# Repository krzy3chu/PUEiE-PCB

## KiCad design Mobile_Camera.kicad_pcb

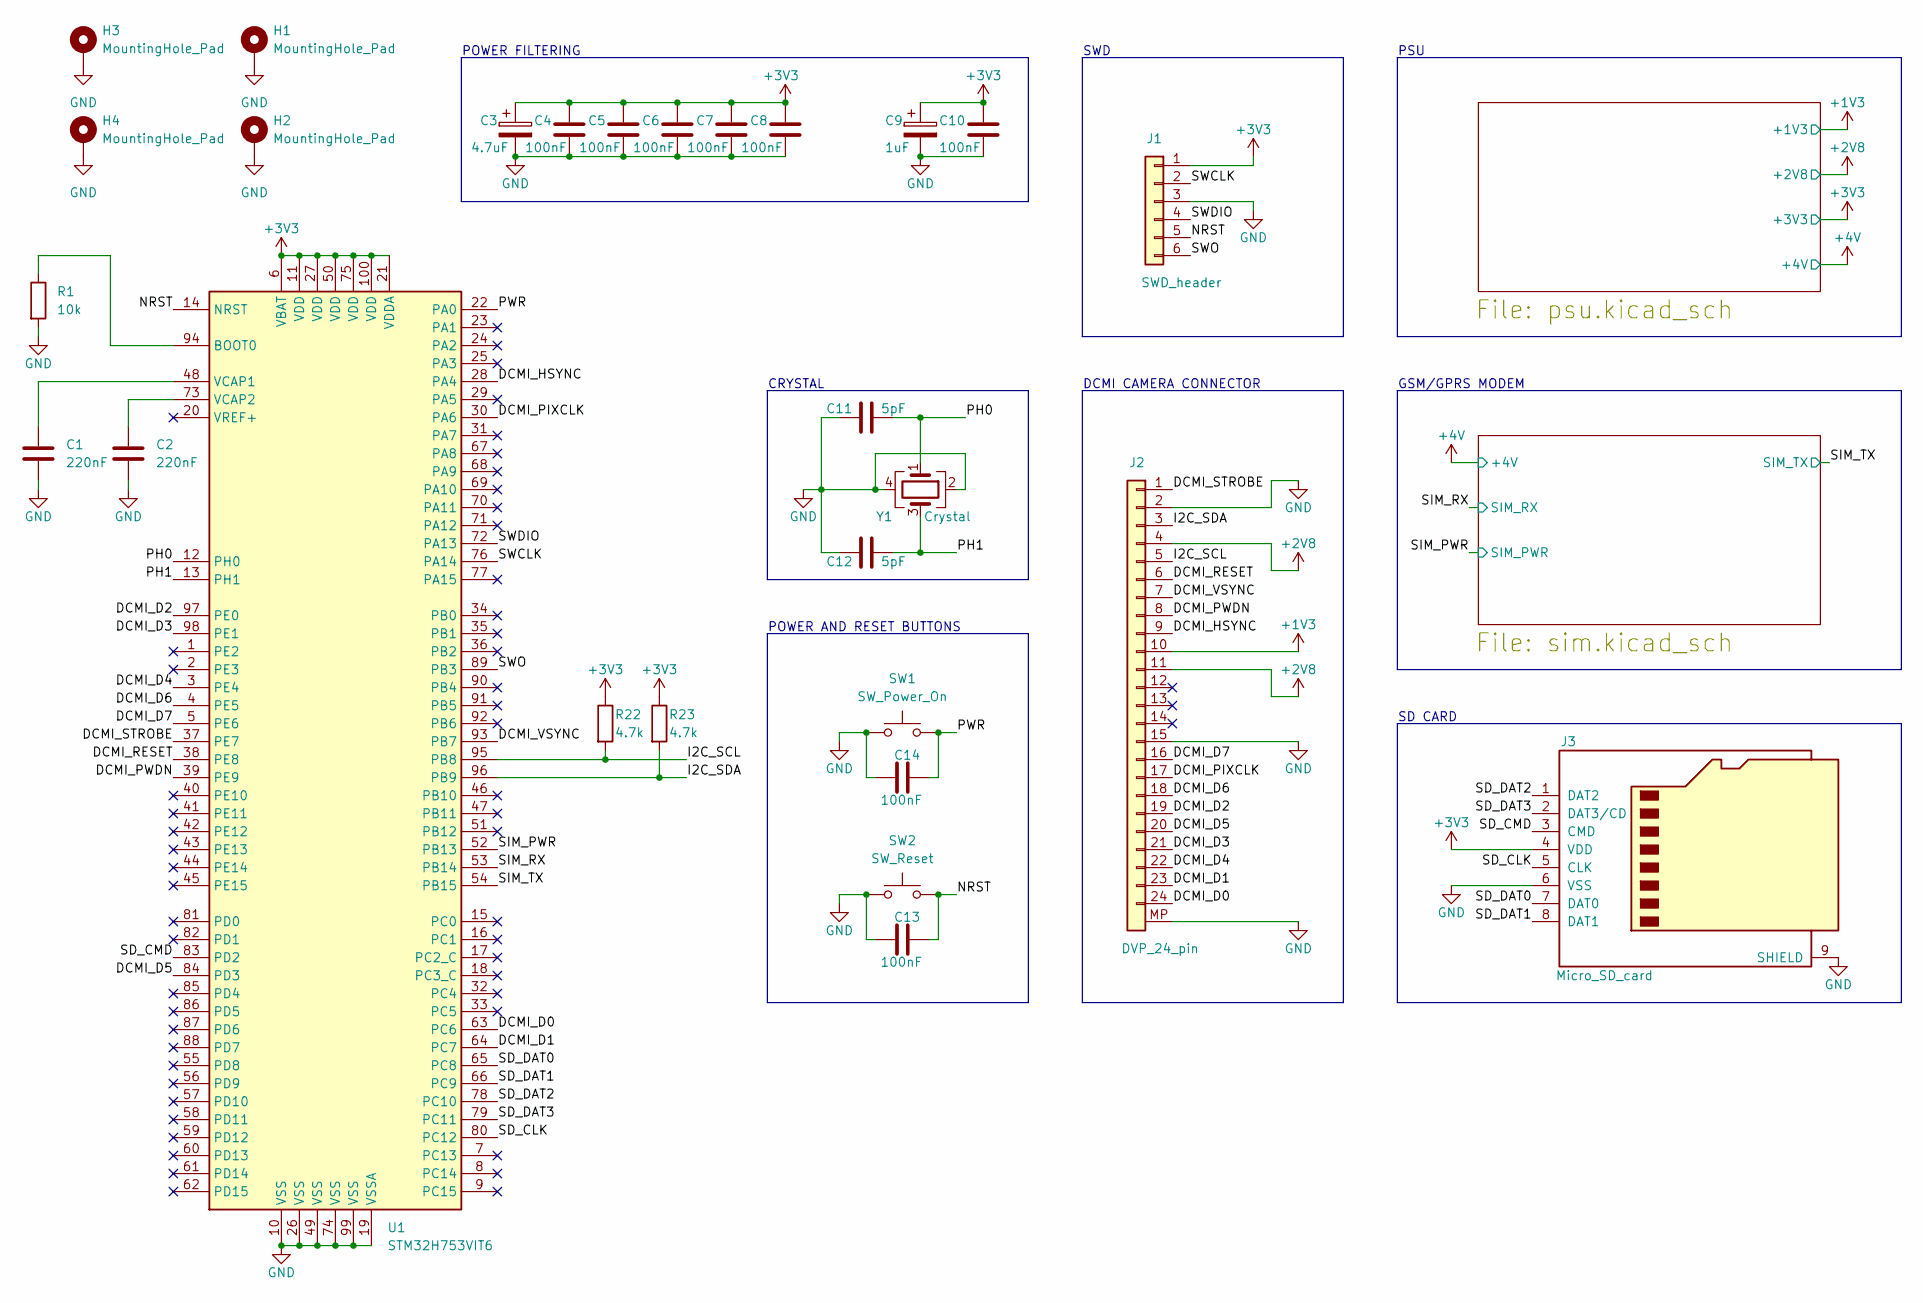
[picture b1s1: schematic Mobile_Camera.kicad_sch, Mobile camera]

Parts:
C1, C2: 220nF; C_0603_1608Metric_Pad1.08x0.95mm_HandSolder
C3: 4.7uF; CP_Elec_4x5.4
C4, C5, C6, C7, C8, C10, C13, C14: 100nF; C_0603_1608Metric_Pad1.08x0.95mm_HandSolder
C9: 1uF; CP_Elec_4x5.4
C11, C12: 5pF; C_0603_1608Metric_Pad1.08x0.95mm_HandSolder
H1, H2, H3, H4: MountingHole_Pad; MountingHole_3.2mm_M3_DIN965_Pad
J1: SWD_header; PinHeader_1x06_P2.54mm_Vertical
J2: DVP_24_pin; TE_2-1734839-4_1x24-1MP_P0.5mm_Horizontal
J3: Micro_SD_card; microSD_HC_Wuerth_693072010801
R1: 10k; R_0603_1608Metric_Pad0.98x0.95mm_HandSolder
R22, R23: 4.7k; R_0603_1608Metric_Pad0.98x0.95mm_HandSolder
SW1: SW_Power_On; SW_SPST_Omron_B3FS-101xP
SW2: SW_Reset; SW_SPST_Omron_B3FS-101xP
U1: STM32H753VIT6; LQFP-100_14x14mm_P0.5mm
Y1: Crystal; Crystal_SMD_SeikoEpson_TSX3225-4Pin_3.2x2.5mm_HandSoldering

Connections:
+1V35: J2.10; also elsewhere on the board
+2V8: J2.4, J2.11; also elsewhere on the board
+3V3: C3.1, C4.1, C5.1, C6.1, C7.1, C8.1, C9.1, C10.1, J1.1, J3.4 (VDD), R22.1, R23.1, U1.6 (VBAT), U1.11 (VDD), U1.21 (VDDA), U1.27 (VDD), U1.50 (VDD), U1.75 (VDD), U1.100 (VDD); also elsewhere on the board
/DCMI_D0: J2.24, U1.63 (PC6)
/DCMI_D1: J2.23, U1.64 (PC7)
/DCMI_D2: J2.19, U1.97 (PE0)
/DCMI_D3: J2.21, U1.98 (PE1)
/DCMI_D4: J2.22, U1.3 (PE4)
/DCMI_D5: J2.20, U1.84 (PD3)
/DCMI_D6: J2.18, U1.4 (PE5)
/DCMI_D7: J2.16, U1.5 (PE6)
/DCMI_HSYNC: J2.9, U1.28 (PA4)
/DCMI_PIXCLK: J2.17, U1.30 (PA6)
/DCMI_PWDN: J2.8, U1.39 (PE9)
/DCMI_RESET: J2.6, U1.38 (PE8)
/DCMI_STROBE: J2.1, U1.37 (PE7)
/DCMI_VSYNC: J2.7, U1.93 (PB7)
/I2C_SCL: J2.5, R22.2, U1.95 (PB8)
/I2C_SDA: J2.3, R23.2, U1.96 (PB9)
/NRST: C13.1, J1.5, SW2.2, U1.14 (NRST)
/PH0: C11.2, U1.12 (PH0), Y1.1
/PH1: C12.2, U1.13 (PH1), Y1.3
/PWR: C14.1, SW1.2, U1.22 (PA0)
/SD_CLK: J3.5 (CLK), U1.80 (PC12)
/SD_CMD: J3.3 (CMD), U1.83 (PD2)
/SD_DAT0: J3.7 (DAT0), U1.65 (PC8)
/SD_DAT1: J3.8 (DAT1), U1.66 (PC9)
/SD_DAT2: J3.1 (DAT2), U1.78 (PC10)
/SD_DAT3: J3.2 (DAT3/CD), U1.79 (PC11)
/SIM_PWR: U1.52 (PB13); also elsewhere on the board
/SIM_RX: U1.53 (PB14); also elsewhere on the board
/SIM_TX: U1.54 (PB15); also elsewhere on the board
/SWCLK: J1.2, U1.76 (PA14)
/SWDIO: J1.4, U1.72 (PA13)
/SWO: J1.6, U1.89 (PB3)
GND: C1.2, C2.2, C3.2, C4.2, C5.2, C6.2, C7.2, C8.2, C9.2, C10.2, C11.1, C12.1, C13.2, C14.2, H1.1, H2.1, H3.1, H4.1, J1.3, J2.2, J2.15, J2.MP, J3.6 (VSS), J3.9 (SHIELD), R1.2, SW1.1, SW2.1, U1.10 (VSS), U1.19 (VSSA), U1.26 (VSS), U1.49 (VSS), U1.74 (VSS), U1.99 (VSS), Y1.2, Y1.4; also elsewhere on the board
unnamed: R1.1, U1.94 (BOOT0)
unnamed: C1.1, U1.48 (VCAP1)
unnamed: C2.1, U1.73 (VCAP2)

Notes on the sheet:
SD CARD
DCMI CAMERA CONNECTOR
PSU
GSM/GPRS MODEM
SWD
POWER FILTERING
POWER AND RESET BUTTONS
CRYSTAL

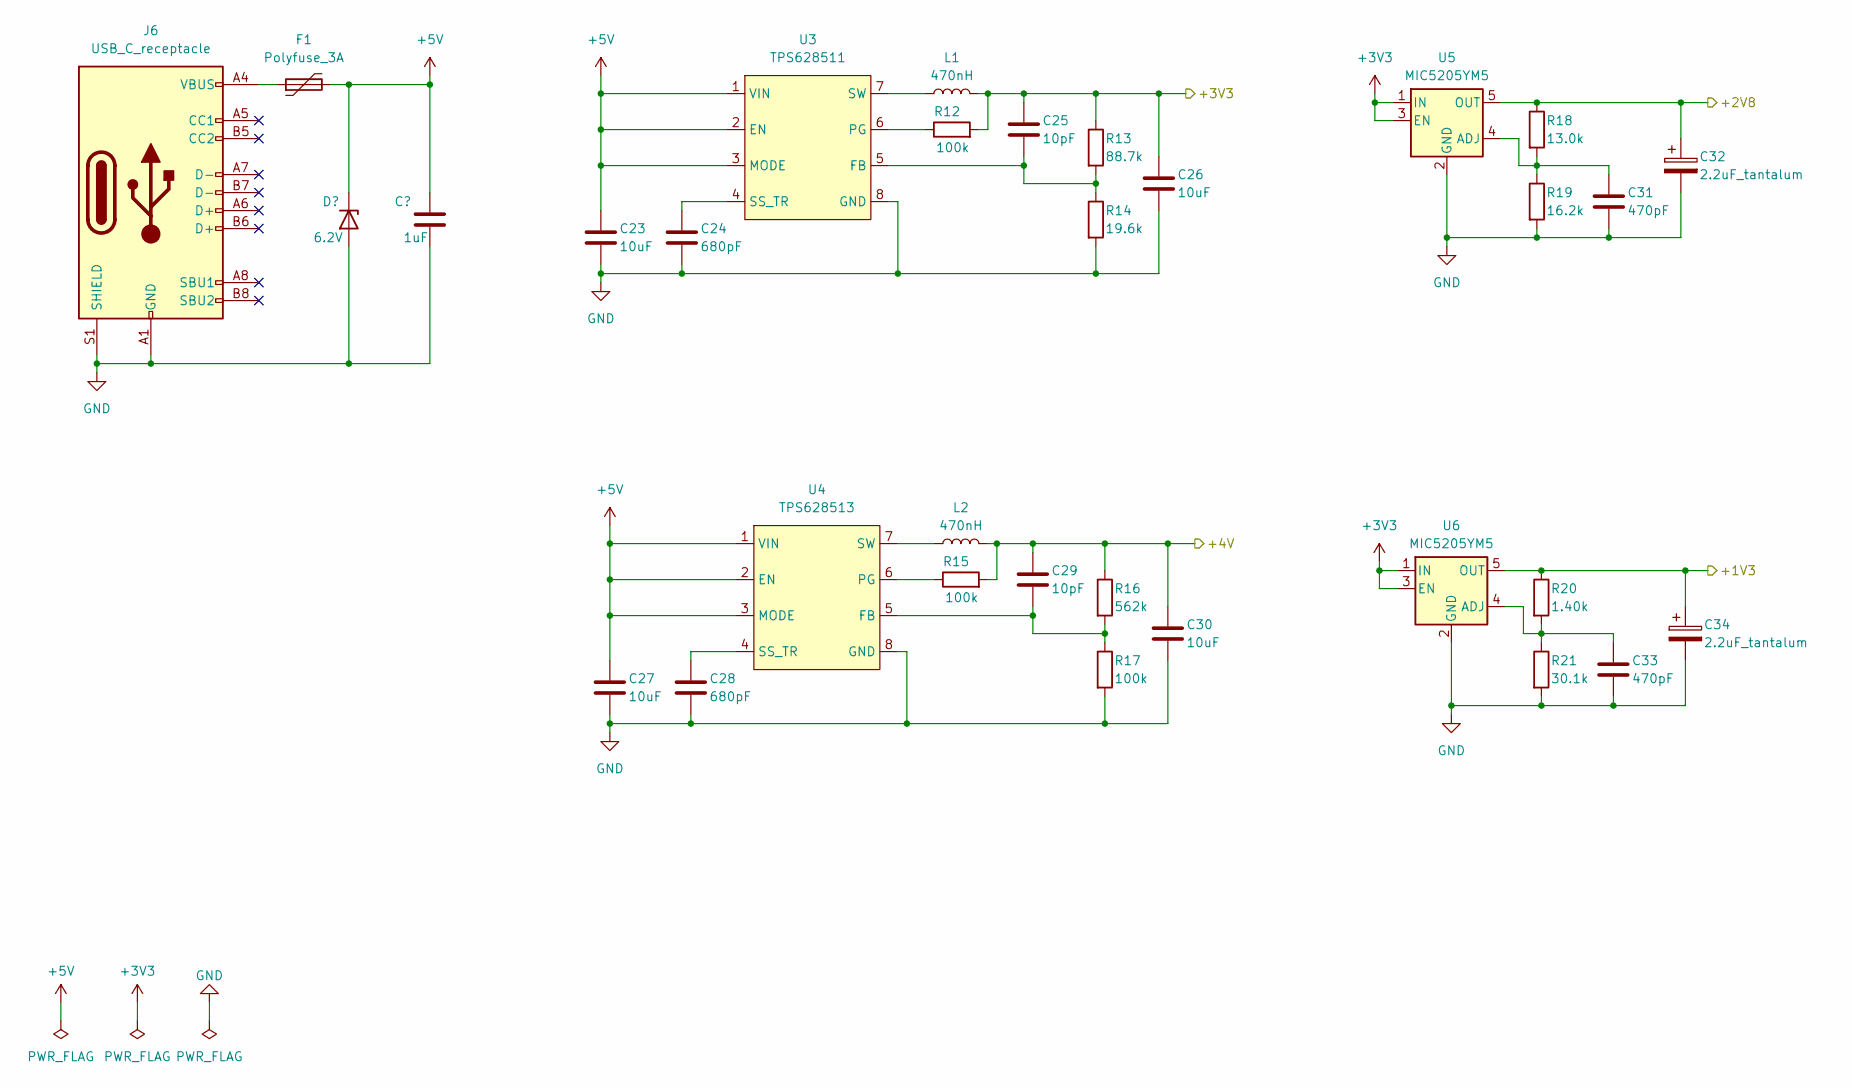
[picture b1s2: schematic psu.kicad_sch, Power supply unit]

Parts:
C22: 1uF; C_0603_1608Metric_Pad1.08x0.95mm_HandSolder
C23, C26, C27, C30: 10uF; C_0603_1608Metric_Pad1.08x0.95mm_HandSolder
C24, C28: 680pF; C_0603_1608Metric_Pad1.08x0.95mm_HandSolder
C25, C29: 10pF; C_0603_1608Metric_Pad1.08x0.95mm_HandSolder
C31, C33: 470pF; C_0603_1608Metric_Pad1.08x0.95mm_HandSolder
C32, C34: 2.2uF_tantalum; C_0603_1608Metric_Pad1.08x0.95mm_HandSolder
D5: 6.2V; D_SOD-323_HandSoldering
F1: Polyfuse_3A; Fuse_1812_4532Metric_Pad1.30x3.40mm_HandSolder
J6: USB_C_receptacle; USB_C_Receptacle_JAE_DX07S016JA1R1500
L1, L2: 470nH; L_Vishay_IHLP-1616
R12, R15, R17: 100k; R_0603_1608Metric_Pad0.98x0.95mm_HandSolder
R13: 88.7k; R_0603_1608Metric_Pad0.98x0.95mm_HandSolder
R14: 19.6k; R_0603_1608Metric_Pad0.98x0.95mm_HandSolder
R16: 562k; R_0603_1608Metric_Pad0.98x0.95mm_HandSolder
R18: 13.0k; R_0603_1608Metric_Pad0.98x0.95mm_HandSolder
R19: 16.2k; R_0603_1608Metric_Pad0.98x0.95mm_HandSolder
R20: 1.40k; R_0603_1608Metric_Pad0.98x0.95mm_HandSolder
R21: 30.1k; R_0603_1608Metric_Pad0.98x0.95mm_HandSolder
U3: TPS628511; SOT-583
U4: TPS628513; SOT-583
U5, U6: MIC5205YM5; SOT-23-5

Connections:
+1V35: C34.1, R20.1, U6.5 (OUT); also elsewhere on the board
+2V8: C32.1, R18.1, U5.5 (OUT); also elsewhere on the board
+3V3: C25.1, C26.1, L1.2, R12.2, R13.1, U5.1 (IN), U5.3 (EN), U6.1 (IN), U6.3 (EN); also elsewhere on the board
+4V: C29.1, C30.1, L2.2, R15.2, R16.1; also elsewhere on the board
+5V: C22.1, C23.1, C27.1, D5.1 (K), F1.2, U3.1 (VIN), U3.2 (EN), U3.3 (MODE), U4.1 (VIN), U4.2 (EN), U4.3 (MODE)
GND: C22.2, C23.2, C24.2, C26.2, C27.2, C28.2, C30.2, C31.2, C32.2, C33.2, C34.2, D5.2 (A), J6.A1 (GND), J6.A12 (GND), J6.B1 (GND), J6.B12 (GND), J6.S1 (SHIELD), R14.2, R17.2, R19.2, R21.2, U3.8 (GND), U4.8 (GND), U5.2 (GND), U6.2 (GND); also elsewhere on the board
unnamed: F1.1, J6.A4 (VBUS), J6.A9 (VBUS), J6.B4 (VBUS), J6.B9 (VBUS)
unnamed: C25.2, R13.2, R14.1, U3.5 (FB)
unnamed: R12.1, U3.6 (PG)
unnamed: C24.1, U3.4 (SS_TR)
unnamed: L1.1, U3.7 (SW)
unnamed: C29.2, R16.2, R17.1, U4.5 (FB)
unnamed: R15.1, U4.6 (PG)
unnamed: C28.1, U4.4 (SS_TR)
unnamed: L2.1, U4.7 (SW)
unnamed: C31.1, R18.2, R19.1, U5.4 (ADJ)
unnamed: C33.1, R20.2, R21.1, U6.4 (ADJ)

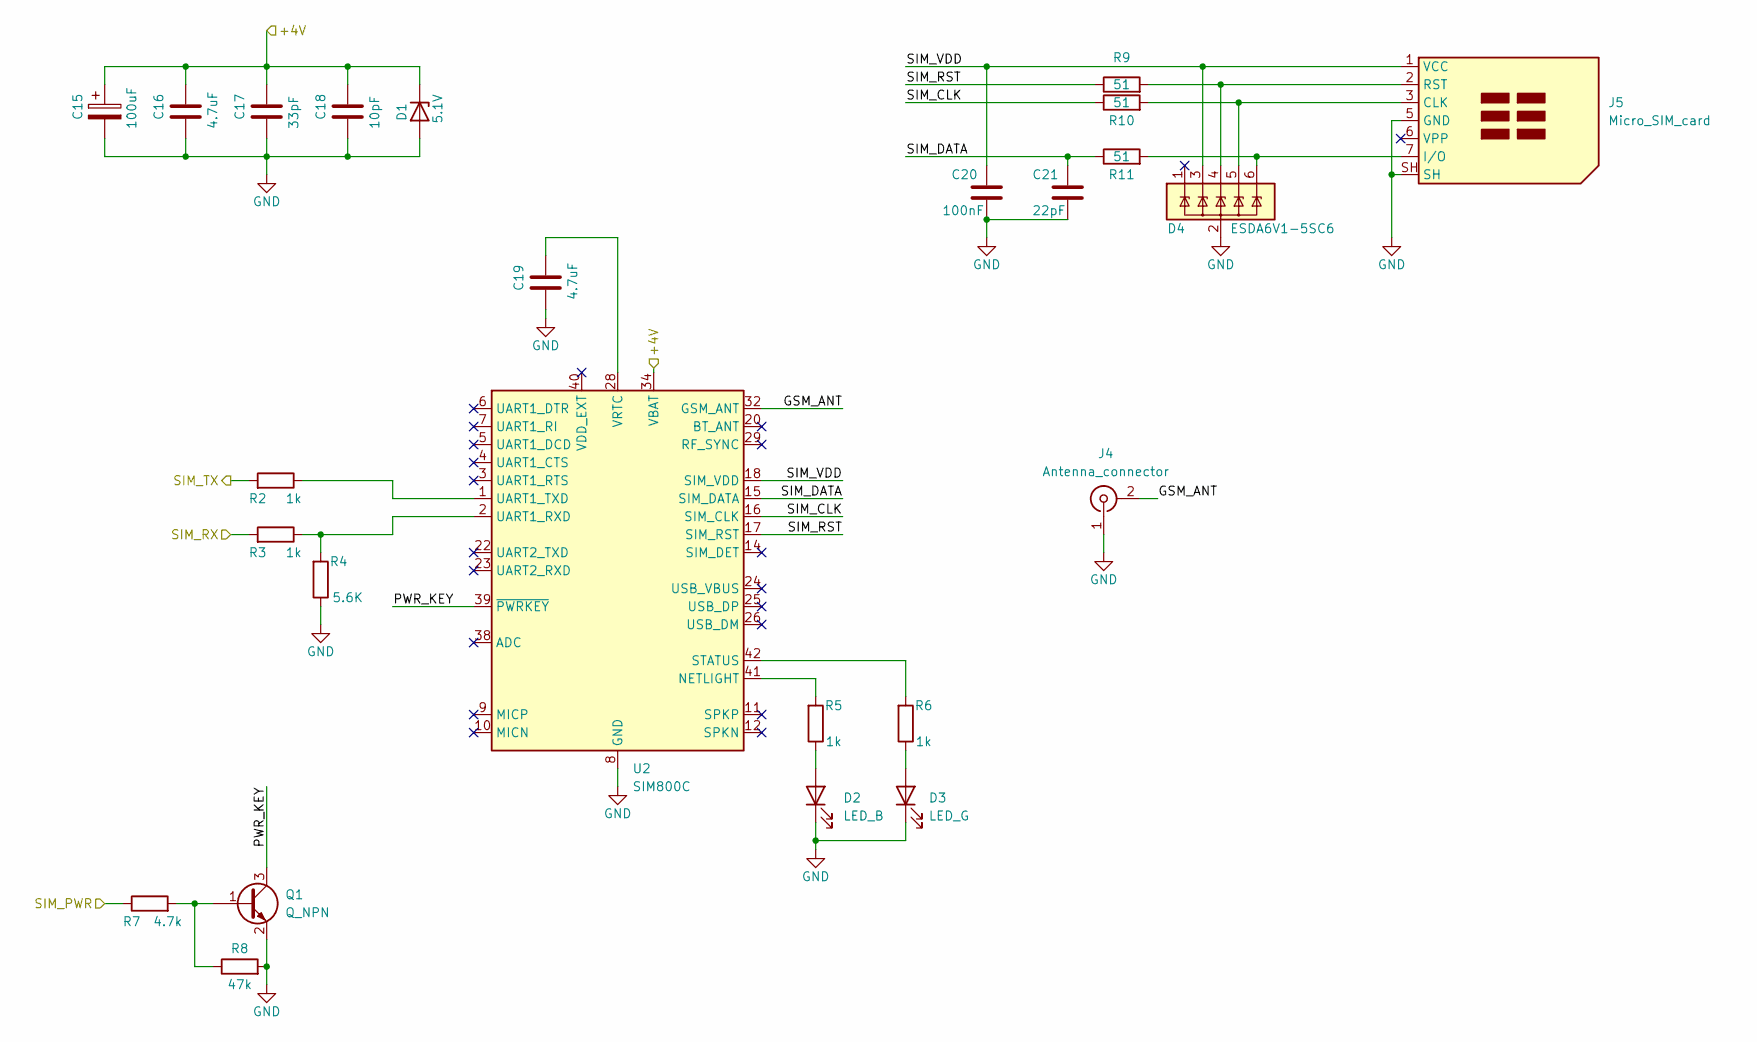
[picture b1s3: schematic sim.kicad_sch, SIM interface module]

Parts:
C15: 100uF; CP_Elec_5x5.4
C16, C19: 4.7uF; C_0603_1608Metric_Pad1.08x0.95mm_HandSolder
C17: 33pF; C_0603_1608Metric_Pad1.08x0.95mm_HandSolder
C18: 10pF; C_0603_1608Metric_Pad1.08x0.95mm_HandSolder
C20: 100nF; C_0603_1608Metric_Pad1.08x0.95mm_HandSolder
C21: 22pF; C_0603_1608Metric_Pad1.08x0.95mm_HandSolder
D1: 5.1V; D_SOD-323_HandSoldering
D2: LED_B; LED_0603_1608Metric
D3: LED_G; LED_0603_1608Metric
D4: ESDA6V1-5SC6; SOT-23-6
J4: Antenna_connector; U.FL_Hirose_U.FL-R-SMT-1_Vertical
J5: Micro_SIM_card; microSIM_JAE_SF53S006VCBR2000
Q1: Q_NPN; SOT-23_Handsoldering
R2, R3, R5, R6: 1k; R_0603_1608Metric_Pad0.98x0.95mm_HandSolder
R4: 5.6K; R_0603_1608Metric_Pad0.98x0.95mm_HandSolder
R7: 4.7k; R_0603_1608Metric_Pad0.98x0.95mm_HandSolder
R8: 47k; R_0603_1608Metric_Pad0.98x0.95mm_HandSolder
R9, R10, R11: 51; R_0603_1608Metric_Pad0.98x0.95mm_HandSolder
U2: SIM800C; SIMCom_SIM800C

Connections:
+4V: C15.1, C16.1, C17.1, C18.1, D1.1 (K), U2.34 (VBAT), U2.35 (VBAT); also elsewhere on the board
/SIM/GSM_ANT: J4.2 (Ext), U2.32 (GSM_ANT)
/SIM/PWR_KEY: Q1.3 (C), U2.39 (~PWRKEY)
/SIM/SIM_CLK: R10.1, U2.16 (SIM_CLK)
/SIM/SIM_DATA: C21.1, R11.1, U2.15 (SIM_DATA)
/SIM/SIM_RST: R9.1, U2.17 (SIM_RST)
/SIM/SIM_VDD: C20.1, D4.3 (IO2), J5.1 (VCC), U2.18 (SIM_VDD)
/SIM_PWR: R7.1; also elsewhere on the board
/SIM_RX: R3.2; also elsewhere on the board
/SIM_TX: R2.2; also elsewhere on the board
GND: C15.2, C16.2, C17.2, C18.2, C19.2, C20.2, C21.2, D1.2 (A), D2.1 (K), D3.1 (K), D4.2 (GND), J4.1 (In), J5.5 (GND), J5.SH, Q1.2 (E), R4.1, R8.2, U2.8 (GND), U2.13 (GND), U2.19 (GND), U2.21 (GND), U2.27 (GND), U2.30 (GND), U2.31 (GND), U2.33 (GND), U2.36 (GND), U2.37 (GND); also elsewhere on the board
unnamed: D2.2 (A), R5.1
unnamed: D3.2 (A), R6.1
unnamed: D4.4 (IO3), J5.2 (RST), R9.2
unnamed: D4.5 (IO4), J5.3 (CLK), R10.2
unnamed: D4.6 (IO5), J5.7 (I/O), R11.2
unnamed: Q1.1 (B), R7.2, R8.1
unnamed: R5.2, U2.41 (NETLIGHT)
unnamed: R6.2, U2.42 (STATUS)
unnamed: R3.1, R4.2, U2.2 (UART1_RXD)
unnamed: R2.1, U2.1 (UART1_TXD)
unnamed: C19.1, U2.28 (VRTC)

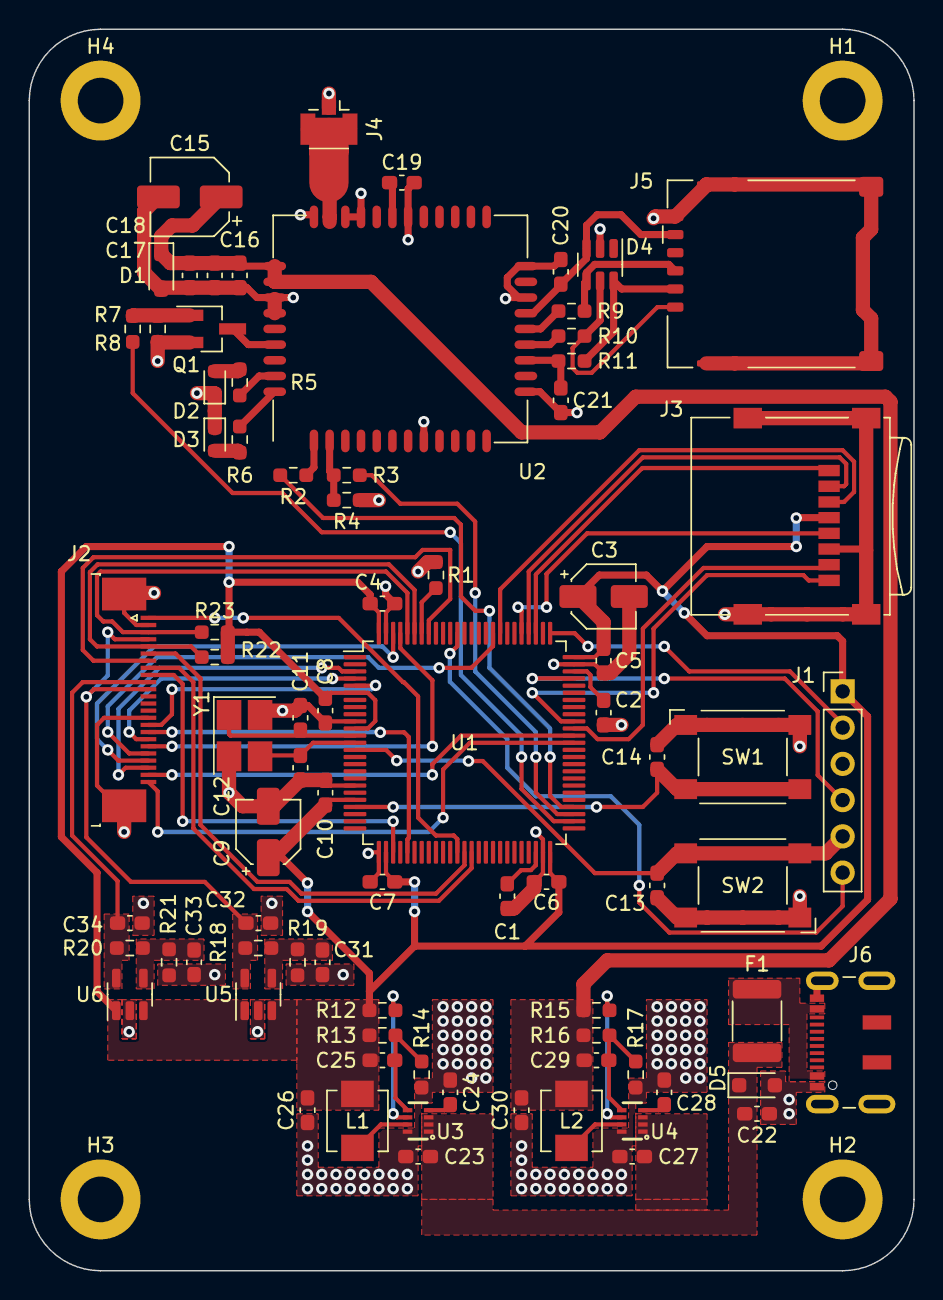
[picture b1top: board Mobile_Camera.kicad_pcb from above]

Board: 2 copper layers, 62.0 x 87.0 mm, 85 parts (0 on the bottom side), 69 nets.

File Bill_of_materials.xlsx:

Item | Reference | Qty | Value / Name | Link | Datasheet
1.0 | C1, C2 | 2.0 | 220nF | https://www.mouser.pl/ProductDetail/KEMET/C0603C224K4RAC7411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
2.0 | C3 | 1.0 | 4.7uF electrolytic | https://www.mouser.pl/ProductDetail/Panasonic/EEE-1CA4R7NR?q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
3.0 | C4, C5, C6, C7, C8, C10, C13, C14, C20 | 9.0 | 100nF | https://www.mouser.pl/ProductDetail/KEMET/C0603C104K5RAC3121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
4.0 | C9 | 1.0 | 1uF electrolytic | https://www.mouser.pl/ProductDetail/Panasonic/EEE-1HA010NR?q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
5.0 | C11, C12 | 2.0 | 5pF | https://www.mouser.pl/ProductDetail/KEMET/C0603C509C5GACAUTO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
6.0 | C15 | 1.0 | 100uF electrolytic | https://www.mouser.pl/ProductDetail/Panasonic/EEE-1AA101WR?q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
7.0 | C16, C19 | 2.0 | 4.7uF | https://www.mouser.pl/ProductDetail/KEMET/C0603C475K9PACTU?q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
8.0 | C17 | 1.0 | 33pF | https://www.mouser.pl/ProductDetail/KEMET/C0603C330K5RACTU?q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
9.0 | C18, C25, C29 | 3.0 | 10pF | https://www.mouser.pl/ProductDetail/KEMET/C0603C100K4RACTU?q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
10.0 | C21 | 1.0 | 1uF | https://www.mouser.pl/ProductDetail/KEMET/C0603C105K3RACTU?q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
11.0 | C22 | 1.0 | 22pF | https://www.mouser.pl/ProductDetail/KEMET/C0603C220K3RACTU?q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
12.0 | C23, C26, C27, C30 | 4.0 | 10uF | https://www.mouser.pl/ProductDetail/KEMET/C0603C106M9PACTU?q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
13.0 | C24, C28 | 2.0 | 680pF | https://www.mouser.pl/ProductDetail/KEMET/C0603C681K5RACTU?q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
14.0 | C31, C33 | 2.0 | 470pF | https://www.mouser.pl/ProductDetail/KEMET/C0603C471K1RACTU?q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
15.0 | C32, C34 | 2.0 | 2.2uF_tantalum | https://www.mouser.pl/ProductDetail/Vishay-Sprague/TMCJ1A225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
16.0 | D1 | 1.0 | 5.1V zener | https://www.mouser.pl/ProductDetail/Nexperia/BZX384-A5V1-QX?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
17.0 | D2 | 1.0 | LED blue | https://www.mouser.pl/ProductDetail/Wurth-Elektronik/150060B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
18.0 | D3 | 1.0 | LED green | https://www.mouser.pl/ProductDetail/Wurth-Elektronik/150060G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
19.0 | D4 | 1.0 | ESDA6V1-5SC6 | https://www.mouser.pl/ProductDetail/STMicroelectronics/ESDA6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
20.0 | D5 | 1.0 | 6.2V zener | https://www.mouser.pl/ProductDetail/Nexperia/BZX384-A6V2-QX?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
21.0 | F1 | 1.0 | Polyfuse_3A | https://www.mouser.pl/ProductDetail/Littelfuse/MINISMDC150F-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
22.0 | J1 | 1.0 | SWD_header | https://www.mouser.pl/ProductDetail/TE-Connectivity/826629-6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
23.0 | J2 | 1.0 | DVP_24_pin
24.0 | J3 | 1.0 | Micro_SD_card | https://www.mouser.pl/ProductDetail/Wurth-Elektronik/6930720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
25.0 | J4 | 1.0 | Antenna_connector
26.0 | J5 | 1.0 | Micro_SIM_card | https://www.mouser.pl/ProductDetail/JAE-Electronics/SF53S006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
27.0 | J6 | 1.0 | USB_C_receptacle | https://www.mouser.pl/ProductDetail/JAE-Electronics/DX07S016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
28.0 | L1, L2 | 2.0 | 470nH | https://www.mouser.pl/ProductDetail/Bourns/SRP4012CC-R47M?qs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
29.0 | Q1 | 1.0 | Q_NPN | https://www.mouser.pl/ProductDetail/onsemi/SMMBT2222ALT1G?qs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
30.0 | R1 | 1.0 | 10k | https://www.mouser.pl/ProductDetail/Panasonic/ERJ-3EKF1002V?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
31.0 | R2, R3, R5, R6 | 4.0 | 1k | https://www.mouser.pl/ProductDetail/Panasonic/ERJ-3EKF4702V?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
32.0 | R4 | 1.0 | 5.6K | https://www.mouser.pl/ProductDetail/Panasonic/ERJ-3EKF5601V?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
33.0 | R7 | 1.0 | 4.7k | https://www.mouser.pl/ProductDetail/Panasonic/ERJ-3EKF4701V?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
34.0 | R8 | 1.0 | 47k | https://www.mouser.pl/ProductDetail/Panasonic/ERJ-3EKF4702V?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
35.0 | R9, R10, R11 | 3.0 | 51.0 | https://www.mouser.pl/ProductDetail/Panasonic/ERJ-3EKF51R0V?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
36.0 | R12, R15, R17 | 3.0 | 100k | https://www.mouser.pl/ProductDetail/Panasonic/ERJ-3EKF1003V?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
37.0 | R13 | 1.0 | 88.7k | https://www.mouser.pl/ProductDetail/Panasonic/ERJ-3EKF8872V?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
38.0 | R14 | 1.0 | 19.6k | https://www.mouser.pl/ProductDetail/Panasonic/ERJ-3EKF1962V?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
39.0 | R16 | 1.0 | 562k | https://www.mouser.pl/ProductDetail/Panasonic/ERJ-3EKF5623V?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
40.0 | R18 | 1.0 | 13.0k | https://www.mouser.pl/ProductDetail/Panasonic/ERJ-3EKF1302V?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
41.0 | R19 | 1.0 | 16.2k | https://www.mouser.pl/ProductDetail/Panasonic/ERJ-3EKF1622V?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
42.0 | R20 | 1.0 | 1.40k | https://www.mouser.pl/ProductDetail/Panasonic/ERJ-3EKF1401V?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
43.0 | R21 | 1.0 | 30.1k | https://www.mouser.pl/ProductDetail/Panasonic/ERJ-3EKF3012V?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
44.0 | SW1 | 1.0 | Switch_reset | https://www.mouser.pl/ProductDetail/Omron-Electronics/B3FS-1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
45.0 | SW2 | 1.0 | Switch_power_on | https://www.mouser.pl/ProductDetail/Omron-Electronics/B3FS-1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
46.0 | U1 | 1.0 | STM32H753VIT6 | https://www.mouser.pl/ProductDetail/STMicroelectronics/STM32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 | http://www.st.com/st-web-ui/static/active/en/resource/techni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
47.0 | U2 | 1.0 | SIM800C | https://www.texim-europe.com/product/wireless-communication-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 | http://simcom.ee/documents/SIM800C/SIM800C_Hardware_Design_V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
48.0 | U3 | 1.0 | TPS628511 | https://www.mouser.pl/ProductDetail/Texas-Instruments/TPS628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 | https://www.ti.com/lit/ds/symlink/tps628513.pdf?HQS=dis-mous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
49.0 | U4 | 1.0 | TPS628513 | https://www.mouser.pl/ProductDetail/Texas-Instruments/TPS628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 | https://www.ti.com/lit/ds/symlink/tps628513.pdf?HQS=dis-mous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
50.0 | U5, U6 | 2.0 | MIC5205YM5 | https://www.mouser.pl/ProductDetail/Microchip-Technology/MIC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 | http://ww1.microchip.com/downloads/en/DeviceDoc/20005785A.pdf
51.0 | Y1 | 1.0 | Crystal
52.0 | _ETERNAL_CAMERA | 1.0 | OV2640 | https://www.arducam.com/product/arducam-ov2640-camera-module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 | https://www.uctronics.com/download/cam_module/OV2640DS.pdf

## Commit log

2023-11-21 Initialize empty KiCad project
2023-11-21 Create scheme for SIM module
2023-12-05 Create scheme for MCU with peripheries
2023-12-06 Change layout
2023-12-06 Add SD card and USB C connections
2023-12-12 Add TSP62851x library and LDO on PSU scheme
2023-12-12 Complete schemes, run ERD check tool.
2023-12-13 Assign footprints, change few elements in scheme
2023-12-13 Create bill of materials
2023-12-13 Add sub-schemes hierarchical labels
2023-12-13 Assign antenna, camera and crystal footprint
2023-12-13 Repair table in scheme
2023-12-14 Complete the schematic, Begin to layout elements
2023-12-14 Partial layout
2023-12-16 Add layout and ednge cut
2023-12-17 Add power delivery routing
2023-12-28 Add controlled impedence trace
2023-12-28 Complete the PCB design
